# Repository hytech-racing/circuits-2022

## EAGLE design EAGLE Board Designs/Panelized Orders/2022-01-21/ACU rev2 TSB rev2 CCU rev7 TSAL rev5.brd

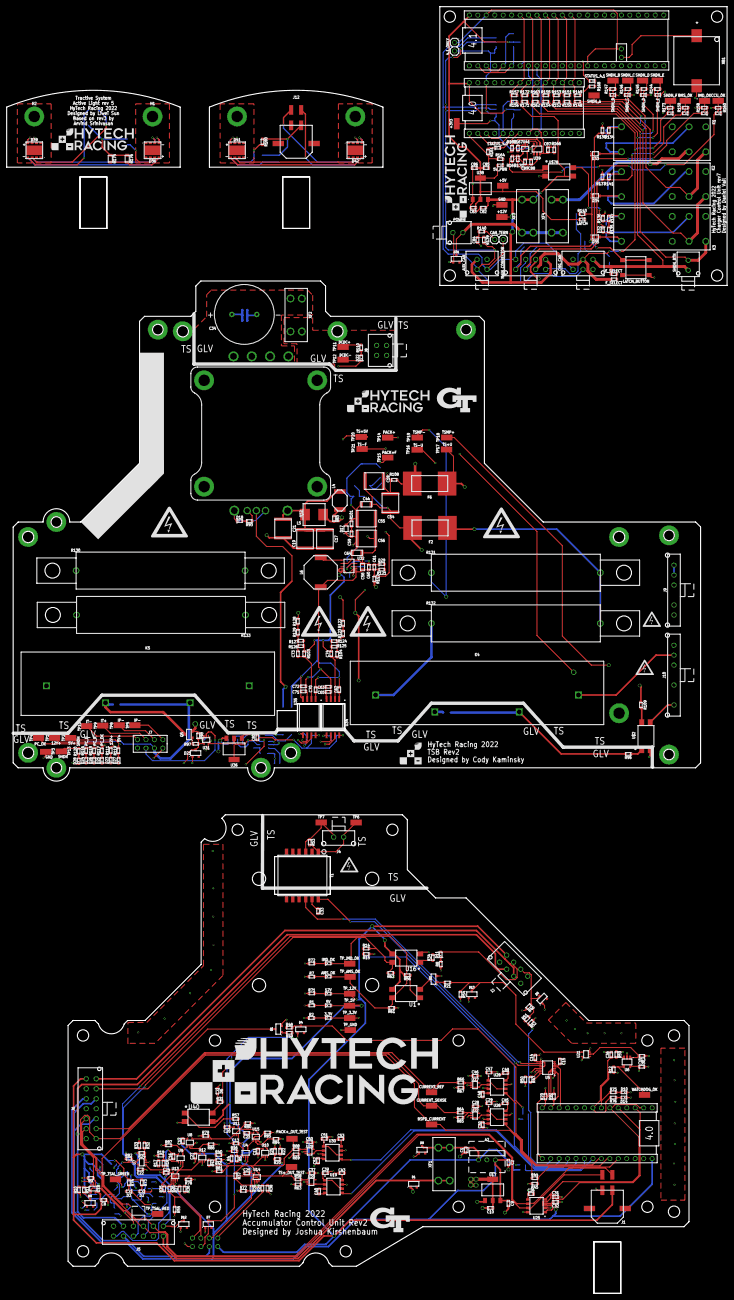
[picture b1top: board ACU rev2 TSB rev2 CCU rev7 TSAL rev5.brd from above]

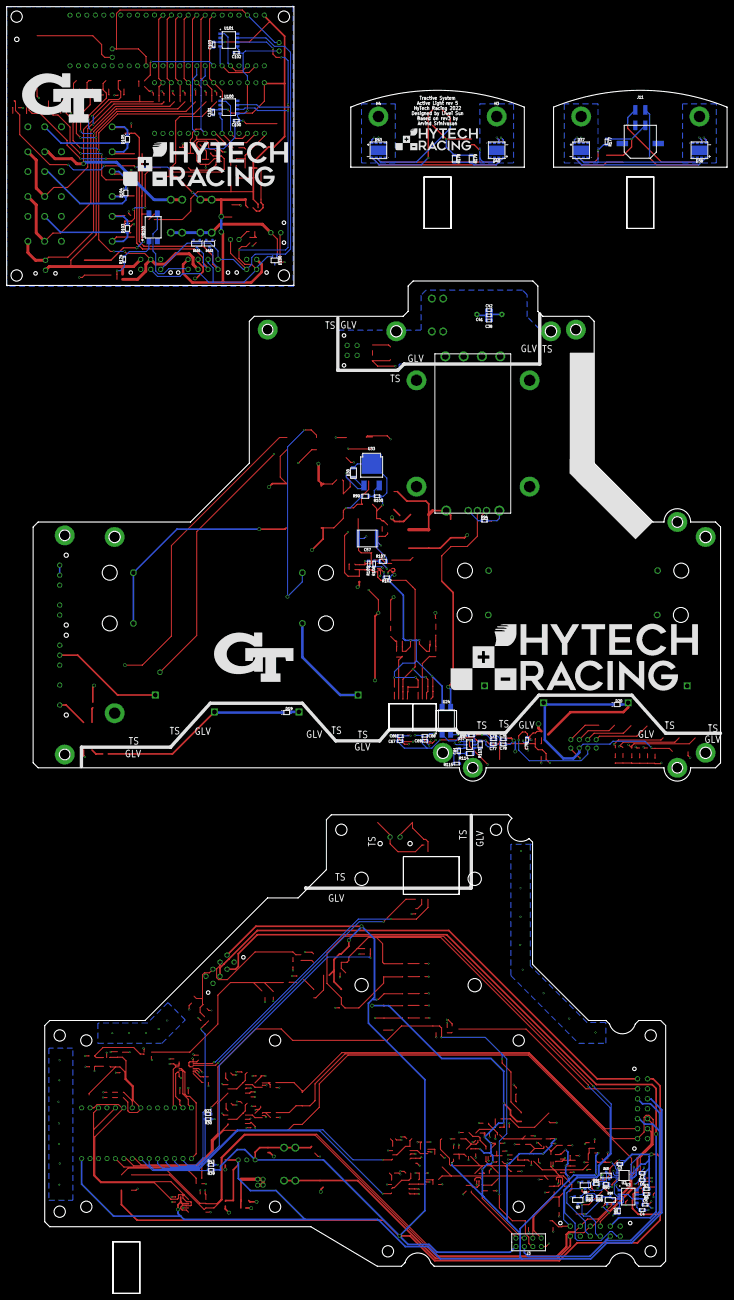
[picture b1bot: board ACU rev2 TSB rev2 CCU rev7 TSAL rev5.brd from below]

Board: 4 copper layers, 216.6 x 386.8 mm, 564 parts (84 on the bottom side), 264 nets.

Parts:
3.3V: LED_0603_GREEN; 0603-LED
4.1_ONLY: JUMPER__1X02; 1X02
5V, 5V_PWR: LED_0603_BLUE; 0603-LED
12V: LED_0603_RED; 0603-LED
A1, A3: TEENSY_4.0; TEENSY_SHORT
A2: VOLTAGE_REGULATOR_MODULE_OKI-78SR_5V; OKI-78SR
A4: TEENSY_4.1; TEENSY_LONG_EXT
AMS_OK: LED_0603_GREEN; 0603-LED
AUX_CAN: CONNECTOR-CAN_MF_T_V_; MOLEX_MICROFIT_PTH_VERTICAL_04_DUAL
BMS_OK: LED_0603_GREEN; 0603-LED
BSPD_CURRENT: TEST_POINT; MICRO_MINIATURE
C1, C2, C38, C82, C83: CAPACITOR_0603_25V_10UF; 0603-CAP
C3, C6, C41, C60, C76: CAPACITOR_0603_25V_1UF; 0603-CAP
C4, C15, C33, C59, C73, C74: CAPACITOR_0603_10V_10NF; 0603-CAP
C5, C10, C77: CAPACITOR_0603_10V_4.7UF; 0603-CAP
C7, C8, C28, C37, C46, C50, C61, C78: CAPACITOR_0603_25V_0.1UF; 0603-CAP
C9, C32, C62, C63, C65, C66, C69, C70, C71, C72, C85: CAPACITOR_0603_10V_1UF; 0603-CAP
C11, C12, C13, C14, C16, C20, C22, C23, C24, C25, C26, C27, C29, C30, C31, C35, C36, C39, C40, C47, C48, C51, C52, C67, C68, C75, C79, C80, C81, C86, C87, C88, C89, C100, C101, C102, C103: CAPACITOR_0603_10V_0.1UF; 0603-CAP
C17, C18: CAPACITOR_2220_630V_0.1UF; 2220-CAP
C19, C21, C54: CAPACITOR_2220_630V_1UF; 2220-CAP
C34: CAPACITOR_POLAR__3600UF; EKYC*MM
C42: CAPACITOR_0603_35V_0.1UF; 0603-CAP
C43, C45, C49, C53: CAPACITOR_0603_10V_680PF; 0603-CAP
C44, C64: CAPACITOR_1206_250V_0.1UF; 1206-CAP
C55, C56, C57: CAPACITOR_2220_250V_1UF; 2220-CAP
C58: CAPACITOR_0805_25V_22UF; 0805-CAP
C84: CAPACITOR_0603_10V_4.7NF; 0603-CAP
CAN_TERM: JUMPER__1X02; 1X02
CCU_OK: LED_0603_GREEN; 0603-LED
CHG_CAN: CONNECTOR-6_MF_T_V_; MOLEX_MICROFIT_PTH_VERTICAL_06_DUAL
CURRENT_REF: TEST_POINT; MICRO_MINIATURE
CURRENT_SENSE: TEST_POINT; MICRO_MINIATURE
D1, D5, D7, D8, D9, D12, D15, D16, D31, D101, D102: TVS_15V; SOT-23
D2, D10, D25: LED_0603_GREEN; 0603-LED
D3, D6, D14, D18, D32: LED_0603_RED; 0603-LED
D4, D13, D21: TVS_8V; SOT-23
D11, D26: LED_0603_YELLOW; 0603-LED
D17, D19, D20, D33, D34, D35, D103, D104, D105: SCHOTTKY_SOD323_30V; SOD-323
D22, D23, D27, D29: LED_0603_BLUE; 0603-LED
D24: LED_0603_WHITE; 0603-LED
D28: LED_0603_ORANGE; 0603-LED
D30: RECTIFIER_400V_SOD123; SOD123F
D36, D37, D38, D39, D40, D41, D42, D43: LED_RGBW_IN-505FCHWV; IN-505FCHWV
D100: TVS_BIDIRECTIONAL_DUAL; SC-70-3
E_SELECT: JUMPER_0603_; 0603-RES
F2, F6: FUSE_0885_1.25; 0885
F_SELECT: JUMPER_0603_; 0603-RES
H1, H2, H3, H4: MOUNTING_HEATSINK_M3; MOUNTING_M3
IMD_OK: LED_0603_ORANGE; 0603-LED
J1: CONNECTOR-CAN_μF_S_RA_; MOLEX_MICROFIT_SMD_RIGHTANGLE_04_DUAL
J2: CONNECTOR-8_MF_T_V_; MOLEX_MICROFIT_PTH_VERTICAL_08_DUAL
J3, J7: CONNECTOR-8_S_S; FLEX_STACK_PTH_08_DUAL
J4: CONNECTOR-2_MF_T_V_; MOLEX_MICROFIT_PTH_VERTICAL_02_SINGLE
J5: CONNECTOR-12_MF_T_V_; MOLEX_MICROFIT_PTH_VERTICAL_12_DUAL
J6: CONNECTOR-14_MF_T_V_; MOLEX_MICROFIT_PTH_VERTICAL_14_DUAL
J8: CONNECTOR-4__; MOLEX_MICROFIT_PTH_VERTICAL_04_DUAL
J9: CONNECTOR-5_MICRO_V6S_; MOLEX_MICROFIT_PTH_VERTICAL_06_SINGLE_SPACED
J10: CONNECTOR-5_MICRO_V7S_; MOLEX_MICROFIT_PTH_VERTICAL_07_SINGLE_SPACED
J11, J12: CONNECTOR-4_μF_S_RA_; MOLEX_MICROFIT_SMD_RIGHTANGLE_04_DUAL
K1, K2, K3: RELAY_DPDT; RT*2*
K4: RELAY_SPST_NC_POLARIZED_3550_12; 335X
K5: RELAY_SPST_NO_3550_12; 335X
L4: INDUCTOR_74451133_3.6UH; 74451133
L5: INDUCTOR_WELMHI_56UH; WE-LMHI
L6: INDUCTOR_SRU1048_330UH; SRU1048
LATCH: LED_0603_WHITE; 0603-LED
LATCH_BUTTON: BUTTON; B3S-100X
MAIN_CONNECTOR: CONNECTOR-8_MF_T_V_; MOLEX_MICROFIT_PTH_VERTICAL_08_DUAL
OKHS: LED_0603_YELLOW; 0603-LED
PACK+_OUT_TEST: TEST_POINT; MICRO_MINIATURE
POWER: CONNECTOR-2_μF_T_V_; MOLEX_MICROFIT_PTH_VERTICAL_02_DUAL
Q1, Q2, Q3, Q4, Q5: TRANSISTOR_N_MOS__PMV15ENEA; SOT-23
R1, R2, R3, R7, R8, R10, R31, R47, R50, R71, R93, R95, R96, R110, R111, R112, R116, R117, R118, R119, R120, R121, R135, R143, R144, R145, R146, R147, R158, R159, R160, R161, R164, R168, R173: RESISTOR_0603_1K; 0603-RES
R4, R18, R22, R32, R40, R94: RESISTOR_0603_DNP; 0603-RES
R5, R17: RESISTOR_0603_4.12K; 0603-RES
R6: RESISTOR_0603_43K; 0603-RES
R9, R12, R48, R54, R55, R58, R59, R60, R61, R62, R64, R66, R68, R77, R78, R79, R80, R81, R82, R84, R85, R86, R87, R89, R91, R98, R101, R136, R137, R138, R165, R166, R169: RESISTOR_0603_10K; 0603-RES
R11: RESISTOR_0603_1.4K; 0603-RES
R13, R167: RESISTOR_0603_100K; 0603-RES
R14, R30, R39, R44, R51, R124, R125, R126, R127, R148, R150, R152, R154, R156, R162, R171: RESISTOR_0603_33K; 0603-RES
R15, R43, R45, R63, R65, R67, R69, R149, R151, R153, R155, R157, R163, R172: RESISTOR_0603_12K; 0603-RES
R16, R19: RESISTOR_0603_10.2K; 0603-RES
R20, R25, R26, R27, R28, R29, R33: RESISTOR_0603_11.5K; 0603-RES
R21, R49, R88, R90, R97: RESISTOR_0603_10; 0603-RES
R23: RESISTOR_0603_18.7K; 0603-RES
R24: RESISTOR_0603_84.5K; 0603-RES
R34, R56, R70, R72, R73, R74, R92: RESISTOR_0603_2K; 0603-RES
R35, R36, R37, R38: RESISTOR_0603_10.5K; 0603-RES
R41: RESISTOR_0603_215K; 0603-RES
R42: RESISTOR_0603_11.3K; 0603-RES
R46: RESISTOR_0603_2.2K; 0603-RES
R52: RESISTOR_0603_15K; 0603-RES
R53: RESISTOR_0603_100; 0603-RES
R57, R75, R76: RESISTOR_0603_470; 0603-RES
R83: RESISTOR_0603_1.62; 0603-RES
R99: RESISTOR_0805_HV365K; 0805-RES
R100: RESISTOR_0603_3.32K; 0603-RES
R102: RESISTOR_0603_75K; 0603-RES
R103, R104: RESISTOR_0603_33.2K; 0603-RES
R105: RESISTOR_0603_8.66K; 0603-RES
R106: RESISTOR_0603_13K; 0603-RES
R107: RESISTOR_0805_976K; 0805-RES
R108, R109: RESISTOR_0603_3.3; 0603-RES
R113: RESISTOR_0805_1M; 0805-RES
R114: RESISTOR_0805_523K; 0805-RES
R115: RESISTOR_0603_154K; 0603-RES
R122, R128: RESISTOR_0603_360K; 0603-RES
R123, R129: RESISTOR_0603_510K; 0603-RES
R130, R131, R132: RESISTOR_B20_10K; B20
R133: RESISTOR_B20_750; B20
R134, R141, R142: RESISTOR_0603_22; 0603-RES
R139, R140: RESISTOR_0603_60.4; 0603-RES
R170, R174: RESISTOR_0603_240; 0603-RES
R175, R176, R178, R179: RESISTOR_0805_56; 0805-RES
R177, R180: RESISTOR_0603_5.1; 0603-RES
SHDN_B: LED_0603_ORANGE; 0603-LED
SHDN_BTN: CONNECTOR-2_μF_T_V_; MOLEX_MICROFIT_PTH_VERTICAL_02_DUAL
SHDN_C: LED_0603_ORANGE; 0603-LED
SHDN_D: LED_0603_ORANGE; 0603-LED
SHDN_E: LED_0603_ORANGE; 0603-LED
SHDN_F: LED_0603_ORANGE; 0603-LED
STATUS_4.0, STATUS_4.1: LED_0603_RED; 0603-LED
T1: TRANSFORMER_HM2112ZNLT_AIRGAP; HM2112ZNLT_AIRGAP
TP1, TP2, TP3, TP4, TP5, TP6, TP7, TP8, TP9, TP10, TP11, TP12, TP13, TP14, TP15, TP16, TP17, TP18, TP19, TP20, TP21: TEST_POINT; MICRO_MINIATURE
TP22, TP23, TP24, TP25, TP26, TP27, TP28, TP29, TP30, TP31, TP32, TP33, TP34: TEST_POINT; 5015
TP_3.3V, TP_5V, TP_12V: TEST_POINT; MICRO_MINIATURE
TP_AMS_OK: TEST_POINT; MICRO_MINIATURE
TP_GND: TEST_POINT; MICRO_MINIATURE
TP_IMD_OK: TEST_POINT; MICRO_MINIATURE
TP_TSAL_GREEN: TEST_POINT; MICRO_MINIATURE
TP_TSAL_RED: TEST_POINT; MICRO_MINIATURE
TS+_OUT_TEST: TEST_POINT; MICRO_MINIATURE
U1, U16, U40: RELAY_SOLIDSTATE_NO; DIP-4
U2: ADG1423; MSOP-10
U3: LM555; SOIC-08(NARROW,0.15")
U4, U7, U9, U10, U12, U13, U14, U18, U20, U22, U27, U29: OPAMP_1_CHANNEL_OPA991; SC-70-5
U5: LTC6820; MSOP-16
U6, U39: ADM8316WBX30; SOT-23-5
U8, U11, U15: LOGICGATE_AND_DCK3; SC-70-5
U17: VOLTAGE_REGULATOR_SOT223_3.3V; SOT223
U19, U26, U28, U30: MAX7404; SOIC-08(NARROW,0.15")
U21, U41: LOGICGATE_BUFFER; SC-70-5
U23: DCM4623TD2J13D0T70; DCM4623
U24: RELAY_SOLIDSTATE_NC_AG; DIP-4_AIRGAP
U25: TCAN1051HQV-Q1; SOIC-08(NARROW,0.15")
U31: LOGICGATE_INVERTER_DCKR; SC-70-5
U32: LTC3639; MSE16(12)
U33: VOLTAGE_REGULATOR_ADJ_LR8_DPAK; DPAK(2-7K1S)
U34, U35: ISO224B_AIRGAP; SOIC-08(WIDE,0.295")-AIRGAP
U36: VOLTAGE_REGULATOR_SOT223_5V; SOT223
U37: LTC6994_1; SOT-23-6
U38: VOLTAGE_REGULATOR_SOT-223_5V; SOT-223
U100, U101: MCP2562FD; SOIC-08(NARROW,0.15")
U$1, U$5, U$56, U$57, U$58, U$59, U$60, U$61, U$62, U$72, U$73, U$74: GLV
U$2, U$78, U$100: RELAY_SOLIDSTATE_NO; DIP-4
U$3, U$9, U$10, U$53, U$63, U$64, U$65, U$66, U$67, U$68, U$69, U$70, U$71, U$75: TS
U$4, U$44, U$45: HV_0.50"
U$6, U$7, U$8, U$11, U$12, U$13, U$14, U$17, U$18, U$19, U$20, U$21, U$22, U$23, U$24, U$25, U$26, U$27, U$28, U$29, U$30, U$31, U$32, U$33, U$34, U$35, U$36, U$37, U$38, U$39, U$40, U$41, U$42, U$49, U$50: MOUNTING_M3
U$15, U$77: LOGO_HYTECH_EXTRA_LARGE
U$16, U$54: LOGO_GT_0.50"
U$43, U$51, U$81, U$82: LOGO_HYTECH_MEDIUM
U$46, U$47: HV_LARGE
U$48, U$52: HV_1.00"
U$55: LOGO_HYTECH_SQUARE_0.28"
U$76, U$80: LOGO_GT_LARGE
U$79: LOGO_HYTECH_LARGE
WATCHDOG_OK: TEST_POINT; MICRO_MINIATURE
XB1: BATTERY_HOLDER_KEYSTONE_498; 498
XF1, XF2, XF3, XF4: FUSE_HOLDER_MINIBLADEPTH; 3568

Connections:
0.95X_DIV: R40.2, R41.2, R42.1, U12.3
0.5989V_DIV: R24.1, R32.2, R33.2, U7.3
2.5_DIV: R20.1, R22.2, R25.2, U10.3
3.56V_DIV_A: R17.1, R18.1, R19.2, U9.1
3.56V_DIV_B: R4.1, R5.1, R16.2, U4.1
4.0_CRX: A3.D0, A3.D4, U100.4
4.0_CTX: A3.D1, A3.D3, U100.1
4.1_CRX: A4.D0, A4.D4, U101.4
4.1_CTX: A4.D1, A4.D3, U101.1
12VIN: D1.3, J5.1, XF1.1, XF1.2
12V_READ: A3.D20, A4.D20, R156.2, R157.1
12V_SCALED_3.3V: A1.D19, R39.2, R43.1
60V_THRESHOLD: R82.2, U2.6, U2.7, U7.4
+3V1: 4.1_ONLY.2, A3.3.3V, C88.2, C89.2, C100.2, C102.2, TP33.1, U39.5, U41.5, U100.5, U101.5
+3V3: 3.3V.2, A1.3.3V, C10.1, C14.1, C15.2, C26.2, C28.1, C30.1, C35.1, C37.1, C40.1, C46.1, C48.1, C50.1, C52.1, R70.2, R92.2, TP_3.3V.1, U5.1, U5.6, U5.7, U5.8, U5.9, U5.12, U6.5, U17.2, U17.4, U19.4, U19.7, U20.5, U21.5, U22.5, U25.5, U26.4, U26.7, U27.5, U28.4, U28.7, U29.5, U30.4, U30.7
+5V: 5V.2, A1.VIN, A2.3, C2.1, C9.1, C11.1, C12.1, C13.1, C16.1, C20.1, C22.1, C23.1, C24.1, C25.1, C27.1, C31.2, C32.2, J6.5, R4.2, R5.2, R17.2, R18.2, R20.2, R24.2, TP_5V.1, U4.5, U7.5, U8.5, U9.5, U10.5, U11.5, U12.5, U13.5, U14.5, U15.5, U17.3, U25.3, U40.4
+5V1: C66.1, C67.1, C68.1, C69.1, C75.1, C77.1, C79.1, C80.1, R113.2, R119.1, TP2.1, U31.5, U34.8, U35.8, U36.2, U36.4, U37.5
+5V2: 5V_PWR.2, A3.VIN, A4.VIN, C83.1, C85.1, C86.2, C101.2, C103.2, LATCH.2, TP28.1, U38.2, U38.4, U100.3, U101.3
+12V: 12V.2, A2.1, C1.1, C3.1, C6.1, C7.1, C8.1, D9.3, J1.1, J2.1, J3.5, J6.7, R3.2, R39.1, R56.2, R73.1, R74.1, TP_12V.1, U1.4, U2.1, U2.2, U2.5, U3.8, U16.4, U18.5, XF1.3, XF1.4
+12V1: C76.1, C78.1, J7.1, R111.2, TP1.1, U36.3
+12V2: AUX_CAN.1, C82.1, MAIN_CONNECTOR.4, R156.1, TP29.1, U38.3, U$78.4, XF3.3, XF3.4
+12V3: J11.1, R175.1, R176.1, R177.1
+12V4: J12.1, R178.1, R179.1, R180.1
ACCUMULATOR_GND: J2.7, J6.14
AIR2-: J6.13, Q1.3
AMS_OK: AMS_OK.2, J5.6, R61.2, TP_AMS_OK.1, U1.3
AMS_OK_3.3V: D13.3, R21.1, R54.1, U21.4
BMS_OK: BMS_OK.2, D101.3, MAIN_CONNECTOR.6, R137.2, R141.2, TP26.1
BSPD_CURRENT: BSPD_CURRENT.1, D8.3, J5.10, R11.2, R44.1, U18.4
BSPD_CURRENT_TEENSY: A1.D22, R44.2, R45.1
CANH: J1.4, J5.9, J6.3, U25.7
CANH1: AUX_CAN.4, CAN_TERM.2, CHG_CAN.4, D100.1, MAIN_CONNECTOR.1, U100.7, U101.7
CANL: J1.3, J5.8, J6.2, U25.6
CANL1: AUX_CAN.3, CHG_CAN.5, D100.2, MAIN_CONNECTOR.2, R139.1, U100.6, U101.6
CCU_OK: CCU_OK.2, R169.2, R170.2, TP24.1, U41.4
CHASSIS_GND: J2.6, J5.11
CS_LTC_6820: A1.D10, U5.5
CURRENT: CURRENT_SENSE.1, J6.8, R9.2, R64.1, U18.1
CURRENT_BUFFER: U22.3, U22.4, U26.2
CURRENT_FILTERED: A1.D21, U26.5
CURRENT_REF: CURRENT_REF.1, J6.9, R66.1
CURRENT_REF_BUFFER: U27.3, U27.4, U28.2
CURRENT_REF_FILTERED: A1.D20, U28.5
DCDC+: J8.1, J8.3, R110.2, TP11.1, XF2.3, XF2.4
DCDC-: C34.-, C38.1, C41.1, C42.1, D22.1, J8.2, J8.4, TP12.1, U23.7, U23.9
ENABLE: U23.3, U24.4
GND: A1.AGND/GND, A1.GND, A2.2, C1.2, C2.2, C3.2, C4.2, C5.2, C6.2, C7.2, C8.2, C9.2, C10.2, C11.2, C12.2, C13.2, C14.2, C15.1, C16.2, C20.2, C22.2, C23.2, C24.2, C25.2, C26.1, C27.2, C28.2, C29.2, C30.2, C31.1, C32.1, C33.2, C35.2, C36.2, C37.2, C39.2, C40.2, C43.2, C45.2, C46.2, C47.2, C48.2, C49.2, C50.2, C51.2, C52.2, C53.2, D1.1, D4.1, D5.1, D6.1, D7.1, D8.1, D9.1, D10.1, D12.1, D13.1, D14.1, D15.1, D16.1, J1.2, J2.4, J3.8, J5.2, J6.4, J6.6, J6.11, Q1.2, Q2.2, Q3.2, Q4.2, R1.1, R2.1, R7.1, R8.1, R9.1, R10.1, R12.1, R13.1, R15.2, R16.1, R19.1, R22.1, R25.1, R30.2, R32.1, R33.1, R36.2, R38.2, R40.1, R41.1, R43.2, R45.2, R46.1, R48.2, R50.2, R52.2, R54.2, R55.1, R59.1, R60.1, R61.1, R62.1, R63.2, R65.2, R67.2, R69.2, R71.1, R72.1, R77.1, R78.1, R79.1, R80.1, R81.1, R82.1, R84.1, R85.1, R86.1, R87.1, R89.2, R91.2, TP_GND.1, U2.4, U2.8, U3.1, U4.2, U5.13, U5.14, U6.2, U7.2, U8.3, U9.2, U10.2, U11.3, U12.2, U13.2, U14.2, U15.3, U16.2, U17.1, U18.2, U19.3, U20.2, U21.3, U22.2, U25.2, U25.8, U26.3, U27.2, U28.3, U29.2, U30.3, U40.2
GND1: C66.2, C67.2, C68.2, C69.2, C75.2, C76.2, C77.2, C78.2, C79.2, C80.2, C81.2, D19.A, D21.1, D23.1, D24.1, D25.1, D26.1, D27.1, D28.1, J7.4, K4.3, Q5.2, R98.1, R114.1, R115.1, TP3.1, U24.2, U31.3, U34.5, U35.5, U36.1, U37.2, U$2.2
GND2: A3.AGND/GND, A3.GND, A4.AGND/GND, A4.GND, A4.GND@2, AUX_CAN.2, C82.2, C83.2, C84.2, C85.2, C86.1, C87.1, C88.1, C89.1, C100.1, C101.1, C102.1, C103.1, CHG_CAN.6, D31.1, D32.1, D100.3, D101.1, D102.1, K1.14, K2.14, K3.14, LATCH_BUTTON.3, LATCH_BUTTON.4, MAIN_CONNECTOR.3, POWER.2, R136.1, R137.1, R138.1, R149.2, R151.2, R153.2, R155.2, R157.2, R158.2, R159.2, R160.2, R161.2, R163.2, R164.2, R165.2, R166.1, R167.2, R168.2, R169.1, R172.2, R173.2, SHDN_B.1, SHDN_C.1, SHDN_D.1, SHDN_E.1, TP27.1, U38.1, U39.2, U41.3, U100.2, U100.8, U101.2, U101.8, U$78.2, U$100.2, U$100.3, XB1.2
GND_GREEN: D39.B-, J11.4
GND_GREEN1: D43.B-, J12.4
GND_RED: D39.A-, J11.3
GND_RED1: D43.A-, J12.3
HV+_OUT_OK: R79.2, U8.4, U11.1
IM: T1.10, U5.10
IMD_OK: D12.3, IMD_OK.2, J5.7, R14.1, R62.2, TP_IMD_OK.1, U16.3
IMD_OK1: D102.3, MAIN_CONNECTOR.5, OKHS.2, R134.2, R138.2, TP25.1
IMD_OK_TEENSY: A1.D16, R14.2, R15.1
IP: T1.12, U5.11
IP+: J7.5, TP5.1, U35.7
IP-: J7.6, TP8.1, U35.6
ISO_PACK+: J3.1, R29.1
ISO_PACK-: J3.2, R28.1, R77.2
ISO_TS+: J3.3, R27.1
ISO_TS-: J3.4, R26.1, R55.2
IT+: J7.7, TP9.1, U34.7
IT-: J7.8, TP10.1, U34.6
LATCH_BUTTON: D33.C, D34.C, D35.C, LATCH_BUTTON.1, LATCH_BUTTON.2, R143.2
LED+: J9.3, R112.2
MHS: D5.3, J2.3, R46.2, R51.1
MHS_TEENSY: A1.D14, R51.2, R52.1
unnamed: 3.3V.1, R2.2
unnamed: 5V.1, R1.2
unnamed: C5.1, R6.1, U3.2, U3.6
unnamed: D6.2, R31.1
unnamed: C4.1, U3.5
unnamed: R3.1, R6.2, U3.7
unnamed: Q1.1, R49.2
unnamed: R34.2, U16.1
unnamed: D11.1, R8.2
unnamed: R27.2, R36.1, U13.1
unnamed: R26.2, R35.1, U13.3
unnamed: R10.2, R11.1, U18.3
unnamed: A1.D11, R92.1, U5.2
unnamed: 12V.1, R71.2
unnamed: R13.2, U6.1, U21.2
unnamed: R56.1, U1.1
unnamed: AMS_OK.1, R7.2
unnamed: D15.3, R90.1, R91.1, TP_TSAL_GREEN.1, U2.9
unnamed: D16.3, R88.1, R89.1, TP_TSAL_RED.1, U3.3
unnamed: Q2.3, U1.2
unnamed: C44.1, C55.1, D17.A, D30.A, R100.2, R101.1, U33.2
unnamed: R29.2, R38.1, U14.1
unnamed: R28.2, R37.1, U14.3
unnamed: D2.2, R73.2
unnamed: A1.D0, A1.D4, U25.4
unnamed: C39.1, U19.1, U19.6
unnamed: IMD_OK.1, R72.2
unnamed: C59.2, R101.2
unnamed: A1.D1, A1.D3, U25.1
unnamed: Q2.1, R21.2
unnamed: C56.1, C57.1, C59.1, C64.1, D17.C, R107.2, U32.3
unnamed: L4.2, R83.1
unnamed: C17.1, C19.1, C21.1, L4.1, L5.1, U23.1
unnamed: D18.2, R93.2
unnamed: R93.1, U23.4
unnamed: R47.1, U5.16
unnamed: R47.2, R50.1, U5.15
unnamed: R94.1, U23.2
unnamed: C33.1, T1.11
unnamed: C34.+, C38.2, C41.2, C42.2, U23.6, U23.8, XF2.1, XF2.2
unnamed: R57.1, U11.4
unnamed: D20.A, K5.3, Q5.3
unnamed: A1.D12, R70.1, U5.3
unnamed: A1.D13, U5.4
unnamed: C43.1, U19.8
unnamed: D3.2, R74.2
unnamed: D10.2, R75.1
unnamed: R58.2, R63.1, U20.1
unnamed: R57.2, U40.1
unnamed: C29.1, U26.1, U26.6
unnamed: C45.1, U26.8
unnamed: R64.2, R65.1, U22.1
unnamed: C47.1, U28.1, U28.6
unnamed: C49.1, U28.8
unnamed: R66.2, R67.1, U27.1
unnamed: C51.1, U30.1, U30.6
unnamed: C53.1, U30.8
unnamed: R68.2, R69.1, U29.1
unnamed: D14.2, R76.1
unnamed: Q3.1, R88.2
unnamed: Q4.1, R90.2
unnamed: C73.1, R103.2, U35.2
unnamed: C74.1, R104.2, U34.2
unnamed: R102.2, U32.11
unnamed: L6.1, U32.1
unnamed: D21.3, R97.1, R98.2, R118.2, U31.4
unnamed: K5.4, R133.1
unnamed: K4.4, R132.2
unnamed: C70.1, U35.1
unnamed: R96.1, U$2.1
unnamed: R109.2, U$2.3
unnamed: Q5.1, R97.2
unnamed: C62.1, U34.1
unnamed: R95.2, U24.1
unnamed: R103.1, R126.2, R127.2, R129.1
unnamed: U32.7, U32.10
unnamed: R104.1, R123.1, R124.2, R125.2
unnamed: C18.1, C54.1, D30.C, R108.2, U33.1
unnamed: D22.2, R110.1
unnamed: D23.2, R111.1
unnamed: R105.2, R106.1, U32.12
unnamed: R106.2, R107.1, U32.14
unnamed: R113.1, R114.2, U37.6
unnamed: C81.1, R115.2, U37.3
unnamed: R95.1, R116.2, U37.4
unnamed: D24.2, R116.1
unnamed: D25.2, R117.1
unnamed: D26.2, R118.1
unnamed: D27.2, R119.2
unnamed: D28.2, R120.1
unnamed: D29.2, R121.1
unnamed: R128.1, R129.2
unnamed: R122.1, R123.2
unnamed: R99.2, R100.1, U33.3
unnamed: D31.3, POWER.1, XF3.1, XF3.2, XF4.1, XF4.2
unnamed: A4.VBAT, XB1.1
unnamed: C84.1, R139.2, R140.1
unnamed: D33.A, D105.A, K1.11, K1.A2
unnamed: D34.A, D104.A, K2.11, K2.A2
unnamed: D105.C, K1.A1, R134.1
unnamed: D104.C, K2.A1, R141.1
unnamed: D103.C, K3.A1, R142.1
unnamed: R135.1, R136.2, R142.2, U$78.3
unnamed: D35.A, D103.A, K3.11, K3.A2
unnamed: D32.2, R135.2
unnamed: LATCH.1, R143.1
unnamed: R144.2, SHDN_E.2
unnamed: R145.2, SHDN_D.2
unnamed: R146.2, SHDN_C.2
unnamed: R147.2, SHDN_B.2
unnamed: OKHS.1, R158.1
unnamed: BMS_OK.1, R159.1
unnamed: CCU_OK.1, R160.1
unnamed: R161.1, STATUS_4.0.1
unnamed: 5V_PWR.1, R164.1
unnamed: 4.1_ONLY.1, A4.3V3, A4.3V3@2, A4.3V3@3
unnamed: R168.1, STATUS_4.1.1
unnamed: R170.1, U$78.1
unnamed: R167.1, U39.1, U41.2
unnamed: R173.1, SHDN_F.1
unnamed: CAN_TERM.1, R140.2
unnamed: E_SELECT.2, F_SELECT.2, R174.1
unnamed: R174.2, U$100.1
unnamed: D37.A-, D38.A+
unnamed: D37.B-, D38.B+
unnamed: D36.A-, D37.A+
unnamed: D36.B-, D37.B+
unnamed: D36.A+, R175.2, R176.2
unnamed: D36.B+, R177.2
unnamed: D36.THERMAL, D37.THERMAL, H1.P$1
unnamed: D38.THERMAL, D39.THERMAL, H2.P$1
unnamed: D38.A-, D39.A+
unnamed: D38.B-, D39.B+
unnamed: D41.A-, D42.A+
unnamed: D41.B-, D42.B+
unnamed: D40.A-, D41.A+
unnamed: D40.B-, D41.B+
unnamed: D40.A+, R178.2, R179.2
unnamed: D40.B+, R180.2
unnamed: D40.THERMAL, D41.THERMAL, H3.P$1
unnamed: D42.THERMAL, D43.THERMAL, H4.P$1
unnamed: D42.A-, D43.A+
unnamed: D42.B-, D43.B+
OKHS: D11.2, J2.2, R34.1
PACK+: J10.5, K5.1, TP14.1, U$2.4
PACK+FUSED: R109.1, R128.2, TP15.1
PACK+_BUFFER: U29.3, U29.4, U30.2
PACK+_FILTERED: A1.D17, U30.5
PACK+_OUT: PACK+_OUT_TEST.1, R37.2, R42.2, R68.1, R81.2, U4.3, U10.1, U14.4
PRECHARGE+_OUT_OK: R80.2, U11.2, U15.4
PRECHARGE_OK: D4.3, D7.3, J3.7, R23.1, R31.2, R48.1, R49.1, U40.3
PRECHARGE_OK1: J7.3, R117.2, TP4.1, U31.2, U37.1
PRECHARGE_OK_TEENSY: A1.D15, R23.2, R30.1
PRECHARGE_REACHED: R86.2, U8.2, U12.4
RPC_SWITCH: MAIN_CONNECTOR.8, U$100.4
SHDN: J3.6, J5.5, J6.10, J6.12
SHDN1: D19.C, D20.C, J7.2, K4.2, K5.2, R96.2, R120.2, TP13.1
SHDN_A: K1.21, R148.1, TP30.1, XF4.3, XF4.4
SHDN_A_READ: A3.D14, A4.D14, R148.2, R149.1
SHDN_B: K1.24, K2.21, R147.1, R150.1, TP31.1
SHDN_B_READ: A3.D15, A4.D15, R150.2, R151.1
SHDN_C: K2.24, K3.21, R146.1, R152.1, TP32.1
SHDN_C_READ: A3.D16, A4.D16, R152.2, R153.1
SHDN_D: K3.24, R145.1, R154.1, SHDN_BTN.1, TP22.1
SHDN_D_READ: A3.D17, A4.D17, R154.2, R155.1
SHDN_E: CHG_CAN.3, E_SELECT.1, R144.1, R162.1, SHDN_BTN.2, TP23.1
SHDN_E_READ: A3.D18, A4.D18, R162.2, R163.1
SHDN_F: CHG_CAN.2, F_SELECT.1, MAIN_CONNECTOR.7, R171.1, SHDN_F.2, TP34.1
SHDN_F_READ: A3.D19, A4.D19, R171.2, R172.1
STATUS_4.0: A3.D5, STATUS_4.0.2
STATUS_4.1: A4.D5, STATUS_4.1.2
SW_SHUTDOWN: A3.D6, A4.D6, C87.2, R166.2, U39.3
TD+: J4.1, R53.2, T1.1, TP6.1
TD-: J4.2, R53.1, T1.3, TP7.1
TEENSY_OK: A1.D6, C36.1, R59.2, R76.2, U6.3
TIMER_EN: R60.2, U2.10, U3.4
TS+5V: C58.1, C60.1, C61.1, C63.1, C65.1, C71.1, C72.1, L6.2, R112.1, R121.2, TP20.1, U32.9, U34.3, U35.3
TS+FUSED: F6.2, J10.4, L5.2, R83.2, R108.1, R122.2
TS+UNFUSED: F6.1, J10.1, J10.2, K4.1, R130.1, R133.2, TP17.1
TS+_OUT: R35.2, R58.1, R78.2, TS+_OUT_TEST.1, U7.1, U9.3, U12.1, U13.4
TS+_OUT_BUFFER: U19.2, U20.3, U20.4
TS+_OUT_FILTERED: A1.D18, U19.5
TS+_OUT_OV_OK: R87.2, U8.1, U9.4
TS-FUSED: C17.2, C18.2, C19.2, C21.2, C44.2, C54.2, C55.2, C56.2, C57.2, C58.2, C60.2, C61.2, C62.2, C63.2, C64.2, C65.2, C70.2, C71.2, C72.2, C73.2, C74.2, D18.1, D29.1, F2.2, J9.1, J9.2, R94.2, R99.1, R102.1, R105.1, R124.1, R125.1, R126.1, R127.1, TP21.1, U23.5, U24.3, U32.6, U32.8, U32.16, U34.4, U35.4
TS-UNFUSED: F2.1, J9.5, R131.1, R132.1, TP16.1
TSAL_GREEN: D2.1, J5.3, Q4.3
TSAL_RED: D3.1, J5.4, Q3.3
TSMP+: J10.3, R130.2, TP18.1
TSMP-: J9.4, R131.2, TP19.1
V_PACK_REF_OV_OK: R85.2, U4.4, U15.1
V_PACK_REF_UV_OK: R84.2, U10.4, U15.2
WATCHDOG_IN: A3.D7, A4.D7, R165.1, U39.4
WATCHDOG_INPUT: A1.D5, R12.2, R75.2, U6.4, WATCHDOG_OK.1

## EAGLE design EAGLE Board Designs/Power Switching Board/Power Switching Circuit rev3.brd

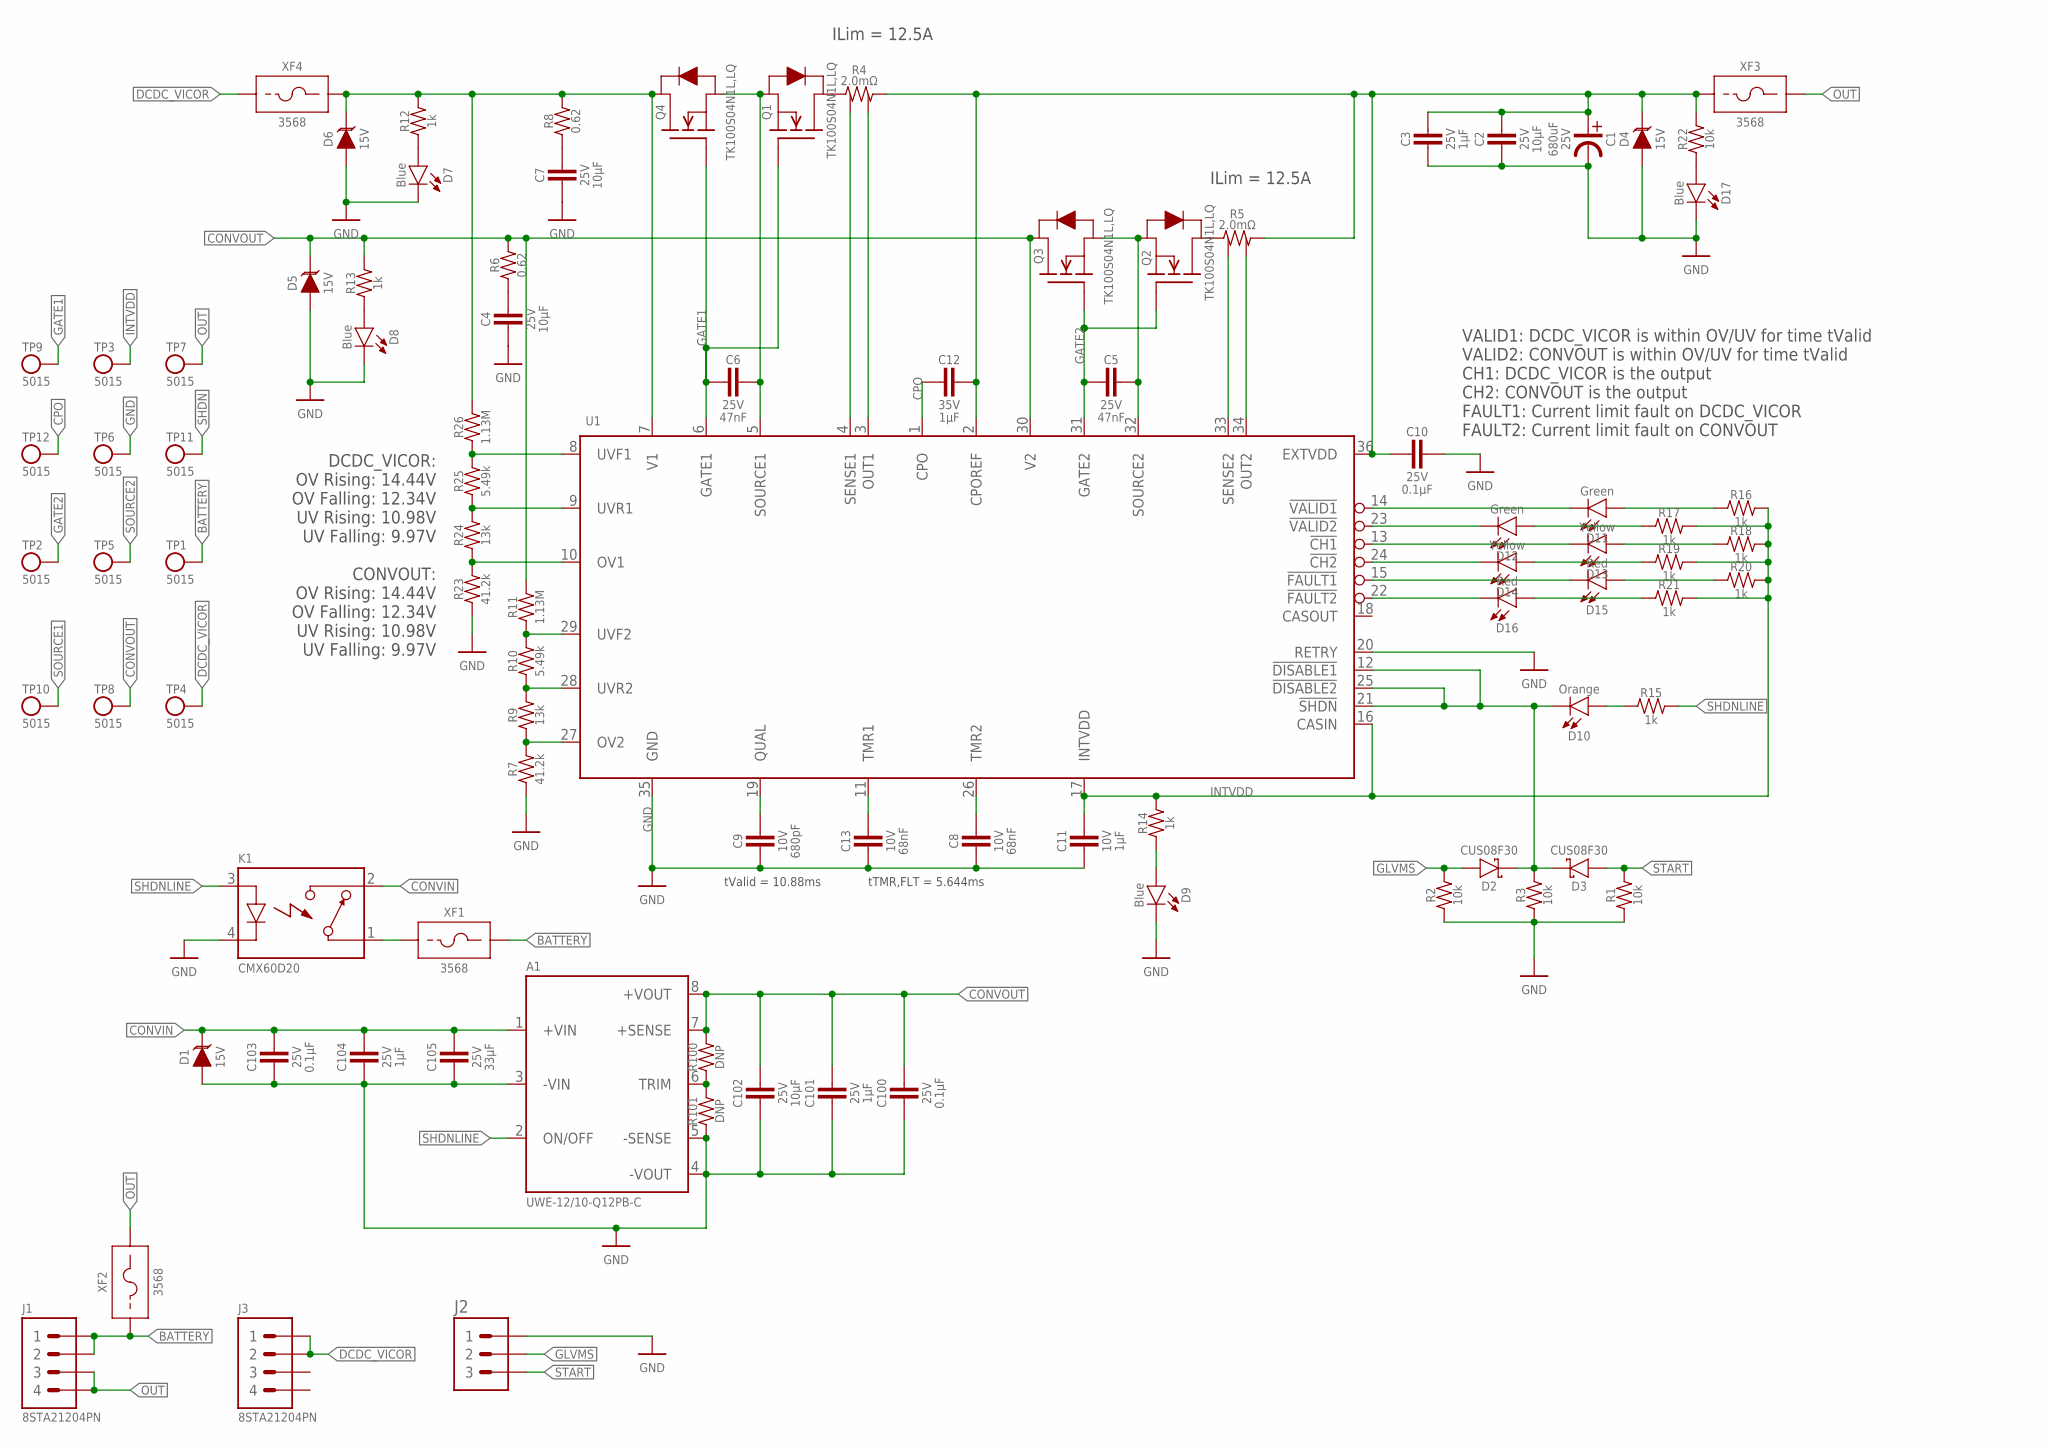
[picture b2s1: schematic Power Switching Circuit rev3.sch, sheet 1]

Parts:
A1: UWE-12/10-Q12PB-C; UWE-*
C1: EEUFP1E681; EEUFP1E*
C2, C4, C7, C102: CAPACITOR_0603_25V_10UF; 0603-CAP
C3, C101, C104: CAPACITOR_0603_25V_1UF; 0603-CAP
C5, C6: CAPACITOR_0603_25V_47NF; 0603-CAP
C8, C13: CAPACITOR_0603_10V_68NF; 0603-CAP
C9: CAPACITOR_0603_10V_680PF; 0603-CAP
C10, C100, C103: CAPACITOR_0603_25V_0.1UF; 0603-CAP
C11: CAPACITOR_0603_10V_1UF; 0603-CAP
C12: CAPACITOR_0603_35V_1UF; 0603-CAP
C105: CAPACITOR_1206_25V_33UF; 1206-CAP
D1, D4, D5, D6: TVS_15V; SOT-23
D2, D3: SCHOTTKY_SOD323_30V; SOD-323
D7, D8, D9, D17: LED_0603_BLUE; 0603-LED
D10: LED_0603_ORANGE; 0603-LED
D11, D12: LED_0603_GREEN; 0603-LED
D13, D14: LED_0603_YELLOW; 0603-LED
D15, D16: LED_0603_RED; 0603-LED
J1, J3: CONNECTOR-4_SOURIAU_; SOURIAU_12-04
J2: CONNECTOR-3_; SOURIAU_04-35
K1: RELAY_SOLIDSTATE_NO_CMX60D20; CRYDOM_CMX
Q1, Q2, Q3, Q4: TRANSISTOR_N_MOS_2-7K1S_TK100S04N1LLQ; DPAK(2-7K1S)
R1, R2, R3, R22: RESISTOR_0603_10K; 0603-RES
R4, R5: RESISTOR_SENSE__WSL40262L000FEB; 4026
R6, R8: RESISTOR_0805_0.62; 0805-RES
R7, R23: RESISTOR_0603_41.2K; 0603-RES
R9, R24: RESISTOR_0603_13K; 0603-RES
R10, R25: RESISTOR_0603_5.49K; 0603-RES
R11, R26: RESISTOR_0603_1.13M; 0603-RES
R12, R13, R14, R15, R16, R17, R18, R19, R20, R21: RESISTOR_0603_1K; 0603-RES
R100, R101: RESISTOR_0603_DNP; 0603-RES
TP1, TP2, TP3, TP4, TP5, TP6, TP7, TP8, TP9, TP10, TP11, TP12: TEST_POINT; 5015
U1: LTC4421; SSOP-36
XF1, XF2, XF3, XF4: FUSE_HOLDER_MINIBLADEPTH; 3568

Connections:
!CH1: D13.1 (C), U1.13 (!CH1)
!CH2: D14.1 (C), U1.24 (!CH2)
!FAULT1: D15.1 (C), U1.15 (!FAULT1)
!FAULT2: D16.1 (C), U1.22 (!FAULT2)
!SHDN: D2.C, D3.C, D10.1 (C), R3.2, TP11.1, U1.12 (!DISABLE1), U1.21 (!SHDN), U1.25 (!DISABLE2)
!VALID1: D11.1 (C), U1.14 (!VALID1)
!VALID2: D12.1 (C), U1.23 (!VALID2)
BATTERY: J1.1, J1.2, TP1.1, XF1.3 (2), XF1.4 (2), XF2.1, XF2.2 (1)
CONVIN: A1.1 (+VIN), C103.1, C104.1, C105.1, D1.3 (C), K1.2 (CONTACT2)
CONVOUT: A1.7 (+SENSE), A1.8 (+VOUT), C100.1, C101.1, C102.1, D5.3 (C), Q3.2 (D), R6.2, R11.2, R13.2, R100.2, TP8.1, U1.30 (V2)
CPO: C12.2, TP12.1, U1.1 (CPO)
DCDC_VICOR: J3.1, J3.2, TP4.1, XF4.1, XF4.2 (1)
DCDC_VICORPREMOS: D6.3 (C), Q4.2 (D), R8.2, R12.2, R26.2, U1.7 (V1), XF4.3 (2), XF4.4 (2)
GATE1: C6.2, Q1.1 (G), Q4.1 (G), TP9.1, U1.6 (GATE1)
GATE2: C5.2, Q2.1 (G), Q3.1 (G), TP2.1, U1.31 (GATE2)
GLVMS: D2.A, J2.B (2), R2.2
GND: A1.3 (-VIN), A1.4 (-VOUT), A1.5 (-SENSE), C1.P$2 (MINUS), C2.2, C3.2, C4.2, C7.2, C8.2, C9.2, C10.1, C11.2, C13.2, C100.2, C101.2, C102.2, C103.2, C104.2, C105.2, D1.1 (A), D4.1 (A), D5.1 (A), D6.1 (A), D7.1 (C), D8.1 (C), D9.1 (C), D17.1 (C), J2.A (1), K1.4 (CONTROL-), R1.1, R2.1, R3.1, R7.1, R23.1, R101.1, TP6.1, U1.20 (RETRY), U1.35 (GND)
INTVDD: C11.1, R14.2, R16.2, R17.2, R18.2, R19.2, R20.2, R21.2, TP3.1, U1.16 (CASIN), U1.17 (INTVDD)
unnamed: C9.1, U1.19 (QUAL)
unnamed: C13.1, U1.11 (TMR1)
unnamed: C8.1, U1.26 (TMR2)
unnamed: C4.1, R6.1
unnamed: D17.2 (A), R22.1
unnamed: D8.2 (A), R13.1
unnamed: D7.2 (A), R12.1
unnamed: D9.2 (A), R14.1
unnamed: D16.2 (A), R21.1
unnamed: K1.1 (CONTACT1), XF1.1, XF1.2 (1)
unnamed: D15.2 (A), R20.1
unnamed: D14.2 (A), R19.1
unnamed: A1.6 (TRIM), R100.1, R101.2
unnamed: D13.2 (A), R18.1
unnamed: R5.3, U1.33 (SENSE2)
unnamed: D12.2 (A), R17.1
unnamed: R5.4, U1.34 (OUT2)
unnamed: D11.2 (A), R16.1
unnamed: C7.1, R8.1
unnamed: R4.3, U1.4 (SENSE1)
unnamed: R24.2, R25.1, U1.9 (UVR1)
unnamed: R23.2, R24.1, U1.10 (OV1)
unnamed: R10.2, R11.1, U1.29 (UVF2)
unnamed: R9.2, R10.1, U1.28 (UVR2)
unnamed: R7.2, R9.1, U1.27 (OV2)
unnamed: D10.2 (A), R15.1
unnamed: Q2.2 (D), R5.1
unnamed: R4.4, U1.3 (OUT1)
unnamed: Q1.2 (D), R4.1
OUT: J1.3, J1.4, TP7.1, XF2.3 (2), XF2.4 (2), XF3.3 (2), XF3.4 (2)
OUTPREFUSE: C1.P$1 (PLUS), C2.1, C3.1, C10.2, C12.1, D4.3 (C), R4.2, R5.2, R22.2, U1.2 (CPOREF), U1.36 (EXTVDD), XF3.1, XF3.2 (1)
SHDNLINE: A1.2 (ON/OFF), K1.3 (CONTROL+), R15.2
SOURCE1: C6.1, Q1.3 (S), Q4.3 (S), TP10.1, U1.5 (SOURCE1)
SOURCE2: C5.1, Q2.3 (S), Q3.3 (S), TP5.1, U1.32 (SOURCE2)
START: D3.A, J2.C (3), R1.2
UVF1: R25.2, R26.1, U1.8 (UVF1)

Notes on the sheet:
DCDC_VICOR: OV Rising: 14.44V OV Falling: 12.34V UV Rising: 10.98V UV Falling: 9.97V CONVOUT: OV Rising: 14.44V OV Falling: 12.34V UV Rising: 10.98V UV Falling: 9.97V
tValid = 10.88ms
tTMR,FLT = 5.644ms
ILim = 12.5A
VALID1: DCDC_VICOR is within OV/UV for time tValid VALID2: CONVOUT is within OV/UV for time tValid CH1: DCDC_VICOR is the output CH2: CONVOUT is the output FAULT1: Current limit fault on DCDC_VICOR FAULT2: Current limit fault on CONVOUT

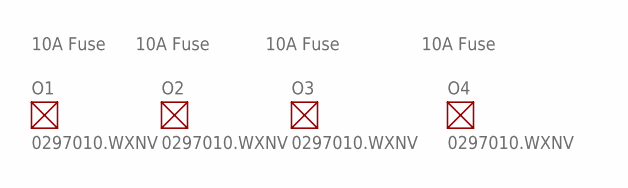
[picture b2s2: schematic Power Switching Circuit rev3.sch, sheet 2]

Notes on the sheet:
10A Fuse

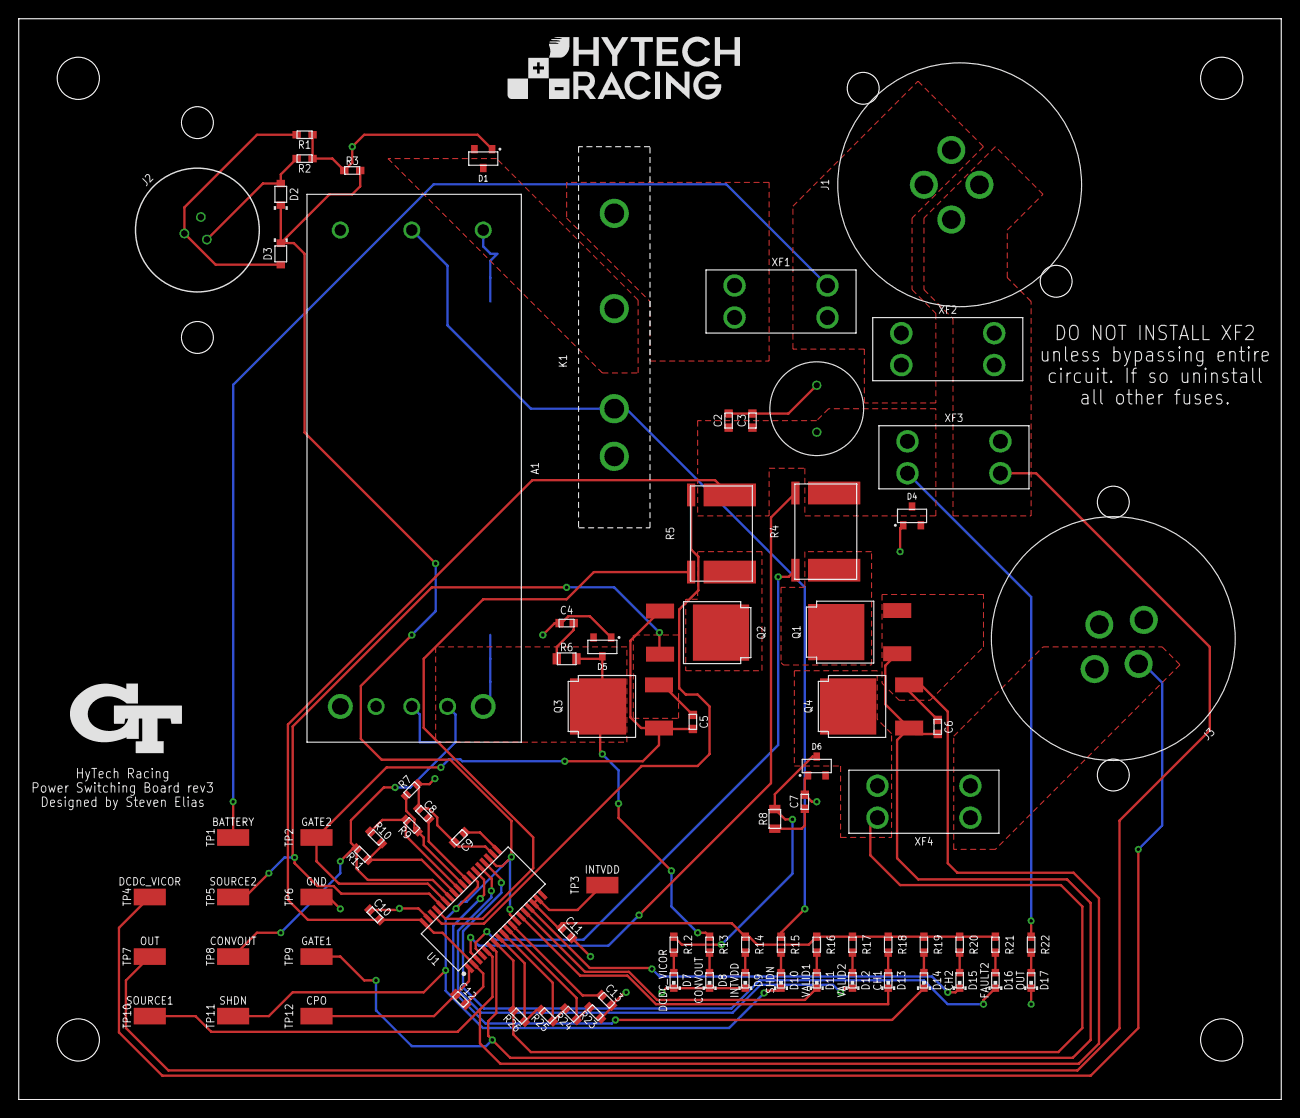
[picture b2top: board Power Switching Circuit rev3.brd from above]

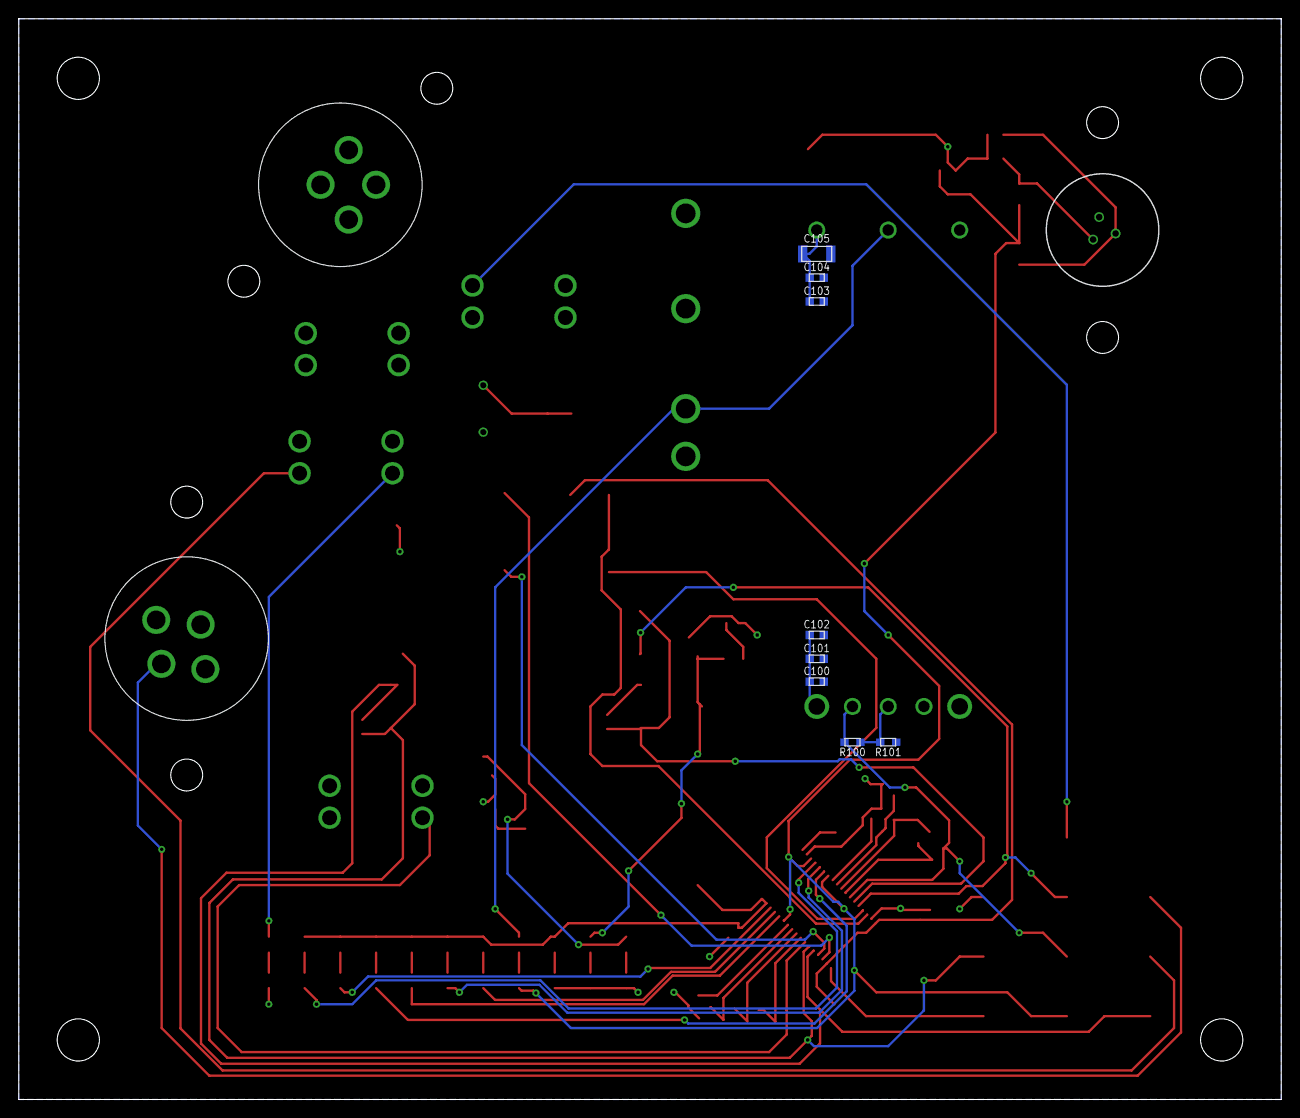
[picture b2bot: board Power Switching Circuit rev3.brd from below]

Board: 2 copper layers, 134.6 x 115.2 mm, 96 parts (8 on the bottom side), 54 nets.

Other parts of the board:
U$1, U$2, U$5, U$6: MOUNTING_M4
U$3: LOGO_HYTECH_MEDIUM
U$4: LOGO_GT_MEDIUM
